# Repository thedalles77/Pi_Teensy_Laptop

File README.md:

# Pi_Teensy_Laptop
Convert a Sony Vaio into a Raspberry Pi and Teensy laptop

The PDF file gives a complete description of the project with pictures and parts list.
The folder contains the Eagle files for a circuit board that connects the Teensy ++2.0 to the keyboard FPC connector.
The .ino file is the Teensyduino C code that scans the keyboard, and touchpad, and controls the video card.
The read_battery.c file is run on the Raspberry Pi to read the registers in the battery with a bit-bang SMBus using 2 of the GPIO pins.
The monitor_battery.c file runs on the Raspberry Pi at startup and monitors battery state of charge every minute over the SMBus.

A short video of this laptop project is at this address: https://vimeo.com/458640649
Battery operation was added after this video was made.

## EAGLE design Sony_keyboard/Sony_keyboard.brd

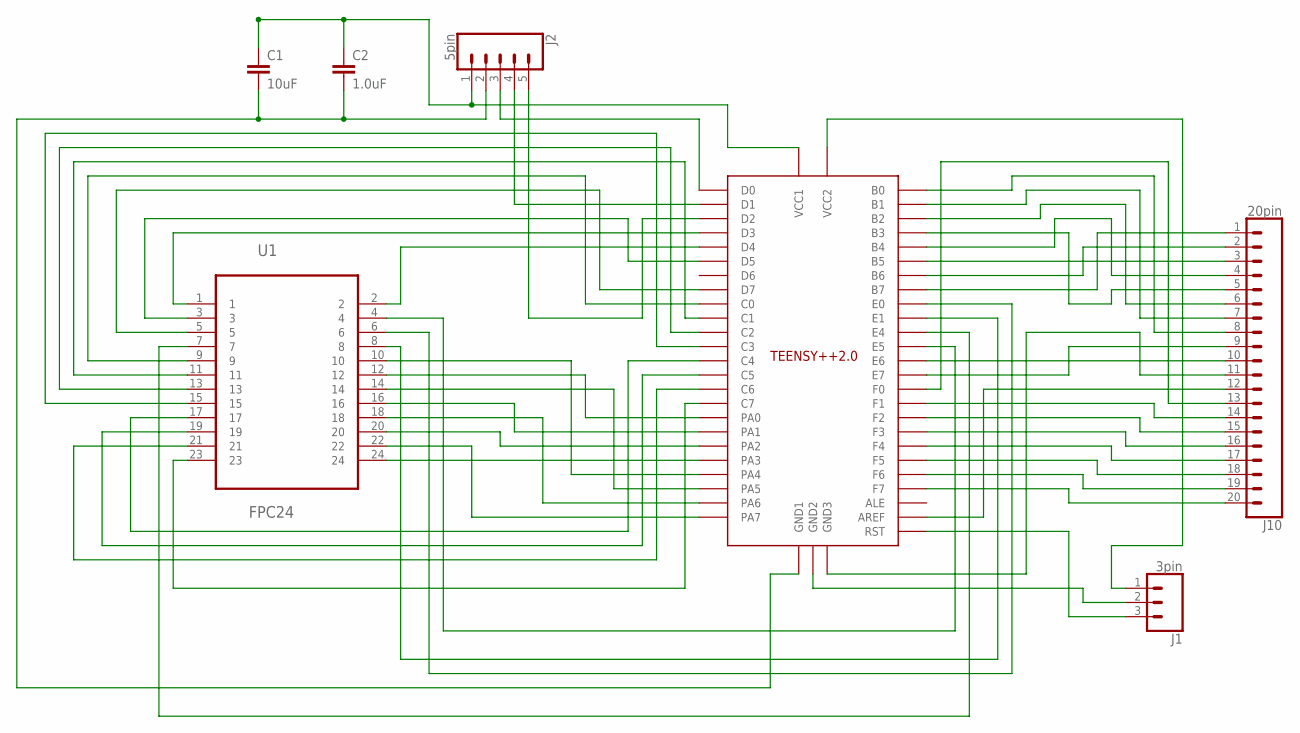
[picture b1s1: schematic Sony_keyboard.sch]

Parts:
C1: 10uF; 0603
C2: 1.0uF; 0603
J1: 3pin; 1X03
J2: 5pin; 1X05
J10: 20pin; 1X20
U1: FPC24
U2: Teensy++2.0; TEENSYPP2.0

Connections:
unnamed: U1.22, U2.PA7
unnamed: U1.18, U2.PA6
unnamed: U1.14, U2.PA5
unnamed: U1.10, U2.PA4
unnamed: U1.24, U2.PA3
unnamed: U1.20, U2.PA2
unnamed: U1.16, U2.PA1
unnamed: U1.12, U2.PA0
unnamed: U1.6, U2.E0
unnamed: U1.8, U2.E1
unnamed: U1.7, U2.E4
unnamed: U1.4, U2.E5
unnamed: U1.1, U2.D3
unnamed: U1.2, U2.D4
unnamed: U1.3, U2.D5
unnamed: U1.5, U2.D7
unnamed: U1.9, U2.C0
unnamed: U1.11, U2.C1
unnamed: U1.13, U2.C2
unnamed: U1.15, U2.C3
unnamed: U1.17, U2.C4
unnamed: U1.19, U2.C5
unnamed: U1.21, U2.C6
unnamed: U1.23, U2.C7
unnamed: J10.18, U2.F5
unnamed: J2.5, U2.D2
unnamed: J2.4, U2.D1
unnamed: J2.3, U2.D0
unnamed: J10.1, U2.B7
unnamed: J10.2, U2.B6
unnamed: J10.3, U2.B5
unnamed: J10.4, U2.B4
unnamed: J10.5, U2.B3
unnamed: J10.6, U2.B2
unnamed: J10.7, U2.B1
unnamed: J10.8, U2.B0
unnamed: J10.9, U2.E7
unnamed: J10.10, U2.E6
unnamed: J10.12, U2.AREF
unnamed: J10.13, U2.F0
unnamed: J10.14, U2.F1
unnamed: J10.15, U2.F2
unnamed: J10.16, U2.F3
unnamed: J10.17, U2.F4
unnamed: J10.19, U2.F6
unnamed: J10.20, U2.F7
unnamed: J1.3, U2.RST
unnamed: C1.1, C2.1, J2.1, U2.VCC1
unnamed: J1.1, U2.VCC2
unnamed: J10.11, U2.GND3
unnamed: J1.2, U2.GND2
unnamed: C1.2, C2.2, J2.2, U2.GND1

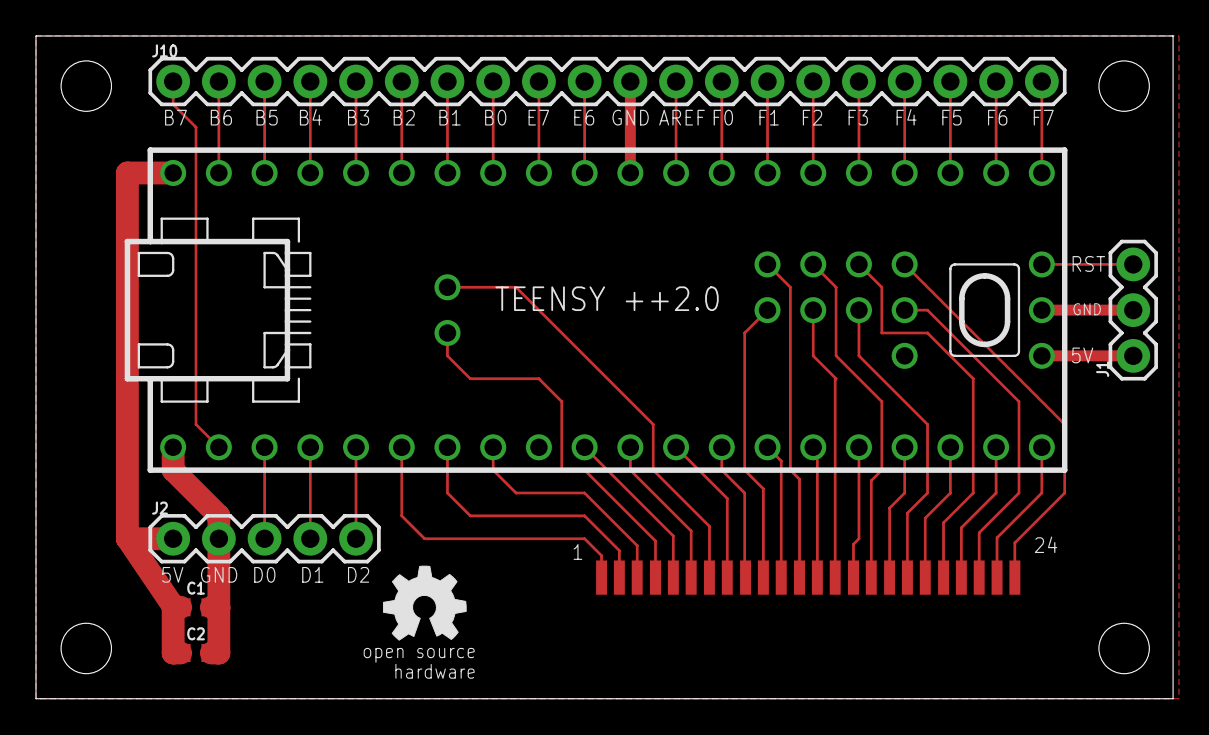
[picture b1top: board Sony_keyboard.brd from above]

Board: 2 copper layers, 63.2 x 36.8 mm, 8 parts (0 on the bottom side), 52 nets.

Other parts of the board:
U$1: OSHW_5MM

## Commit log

2018-10-27 Create LICENSE
2018-12-04 Update LICENSE
2018-12-04 Added Solderpad Hardware License Version 0.51
2021-10-15 Update LICENSE
    Update Solderpad hardware license to 2.1

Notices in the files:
parts and their libraries:
SparkFun-Capacitors: Licensing: Creative Commons ShareAlike 4.0 International - https://creativecommons.org/licenses/by-sa/4.0
